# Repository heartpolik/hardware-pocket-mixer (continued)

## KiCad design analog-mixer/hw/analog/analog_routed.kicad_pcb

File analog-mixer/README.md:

# analog-mixer — Rev A

Портативний аналоговий стереомікшер Rev A: 4 стереоканали з pan і FX-петлею
(send/return), Master L/R, вихід на навушники, OLED-метри та Mute/Solo через ESP32-C3,
живлення від 2S LiPo з USB-C.

> [!WARNING]
> Стан: крок E — схеми (ERC чистий) і обидві плати розведено, DRC без розривів і порушень міді;
> Gerber, свердління й BOM — у `hw/fab/` ([14-kicad.md](docs/14-kicad.md), п. 6). Плати ще не
> замовлені й не перевірені в залізі. Команди з документації запускати з теки `analog-mixer/`.

## Архітектура

```mermaid
flowchart TB
    subgraph DIG["Цифрова плата (верхня, над задніми джеками)"]
        ESP["ESP32-C3 SuperMini<br/>радіо вимкнене"]
        OLED["OLED 128×64<br/>метри, Mute/CLIP Master"]
        ENC["Енкодер"]
        LED["RGB LED ×5"]
        ADC[("АЦП метрів")]
    end
    subgraph ANA["Аналогова плата (нижня)"]
        IN(["IN1–4, RET<br/>задній торець"])
        CTRL["Фейдери ×7, send ×4,<br/>pan ×4, PHONES"]
        AUD["Буфери, суматори,<br/>ключі DG413"]
        MX["Cherry MX ×6<br/>Mute"]
        PWR["2S LiPo → ±12 V, 5 V"]
        OUT(["MAIN, SEND, PHONES"])
    end
    USB(["USB-C<br/>правий торець"]) --> PWR
    USB -.->|"дані: CH340N → UART"| ESP
    IN --> AUD --> OUT
    CTRL --> AUD
    ESP <-->|"I²C-A"| AUD
    MX --> ESP
    AUD -.->|"DC метрів"| ADC --> ESP
    PWR -->|"5 V"| DIG
    ESP --> OLED & LED
    ENC --> ESP
```

## Хід роботи

```mermaid
flowchart LR
    S0["0. Аналоги"]:::done --> SA["A. Фейдери"]:::done --> SB["B. Механіка"]:::done --> SC["C. Схема"]:::done --> SD["D. Pinout між платами"]:::done --> SE["E. KiCad"]:::now
    classDef done fill:#d4edda,stroke:#2a6
    classDef now fill:#ffe9b3,stroke:#b8860b
```

## Документація

| Документ | Зміст |
|---|---|
| [spec-rev-a.md](docs/spec-rev-a.md) | ТЗ |
| [decisions.md](docs/decisions.md) | Журнал рішень D1–D50, має пріоритет над ТЗ |
| [00-prior-art.md](docs/00-prior-art.md) | Аналоги та схожі проєкти |
| [01-faders.md](docs/01-faders.md) | Фейдери Alps RS45 |
| [02-mixerli-analysis.md](docs/02-mixerli-analysis.md) | Розбір mixerli v2.0.1 |
| [03-power-2s.md](docs/03-power-2s.md) | Живлення 2S |
| [04-mixerli-datasheets.md](docs/04-mixerli-datasheets.md) | Висновки з datasheets mixerli |
| [05-mechanics.md](docs/05-mechanics.md) | Механіка, компоновка, висоти |
| [06-signal-flow.md](docs/06-signal-flow.md) | Signal flow, Mute/Solo, метри, керування |
| [07-gain-structure.md](docs/07-gain-structure.md) | Рівні по тракту, запас, шум, вибір op-amp |
| [08-meter-detector.md](docs/08-meter-detector.md) | Детектор метрів і CLIP |
| [09-sourcing.md](docs/09-sourcing.md) | Наявність і ціни ключових компонентів |
| [10-passives.md](docs/10-passives.md) | Пасивні компоненти: правила, перелік, кількості |
| [11-power.md](docs/11-power.md) | Розрахунок живлення ±12 V і 5 V, час роботи |
| [12-parts.md](docs/12-parts.md) | Вибір решти компонентів |
| [13-interboard.md](docs/13-interboard.md) | Крок D: роз'єм і pinout між платами |
| [calc/](docs/calc/), [sim/](docs/sim/) | Скрипти розрахунків (Python) і симуляцій (ngspice) |
| [hw/lib/](hw/lib/README.md) | Бібліотека KiCad: футпринти з креслень |
| [14-kicad.md](docs/14-kicad.md) | Крок E: як згенеровано схеми й плати, стан ERC/DRC |
| [15-3d.md](docs/15-3d.md) | 3D-моделі й збірка |
| [datasheets/](docs/datasheets/README.md) | Усі datasheets проєкту |

## Походження та ліцензія

Проєкт є похідним від **mixerli** (Stahl, 2023):
<https://github.com/stahlnow/mixerli> (базова версія — коміт `18a4a8e`).

SPDX-License-Identifier: CERN-OHL-S-2.0+

This source describes Open Hardware and is licensed under the CERN-OHL-S v2
or any later version. You may redistribute and modify this source and make
products using it under the terms of the CERN-OHL-S v2 or any later version
(https://ohwr.org/cern_ohl_s_v2.txt). This source is distributed WITHOUT ANY
EXPRESS OR IMPLIED WARRANTY, INCLUDING OF MERCHANTABILITY, SATISFACTORY QUALITY
AND FITNESS FOR A PARTICULAR PURPOSE. Please see the CERN-OHL-S v2 for applicable
conditions.

Source location (original): https://github.com/stahlnow/mixerli
Source location (this project): https://github.com/heartpolik/hardware-pocket-mixer

Згідно з розд. 4 CERN-OHL-S v2, на PCB має бути видно source location.
Повний текст ліцензії: [LICENSE](../LICENSE).

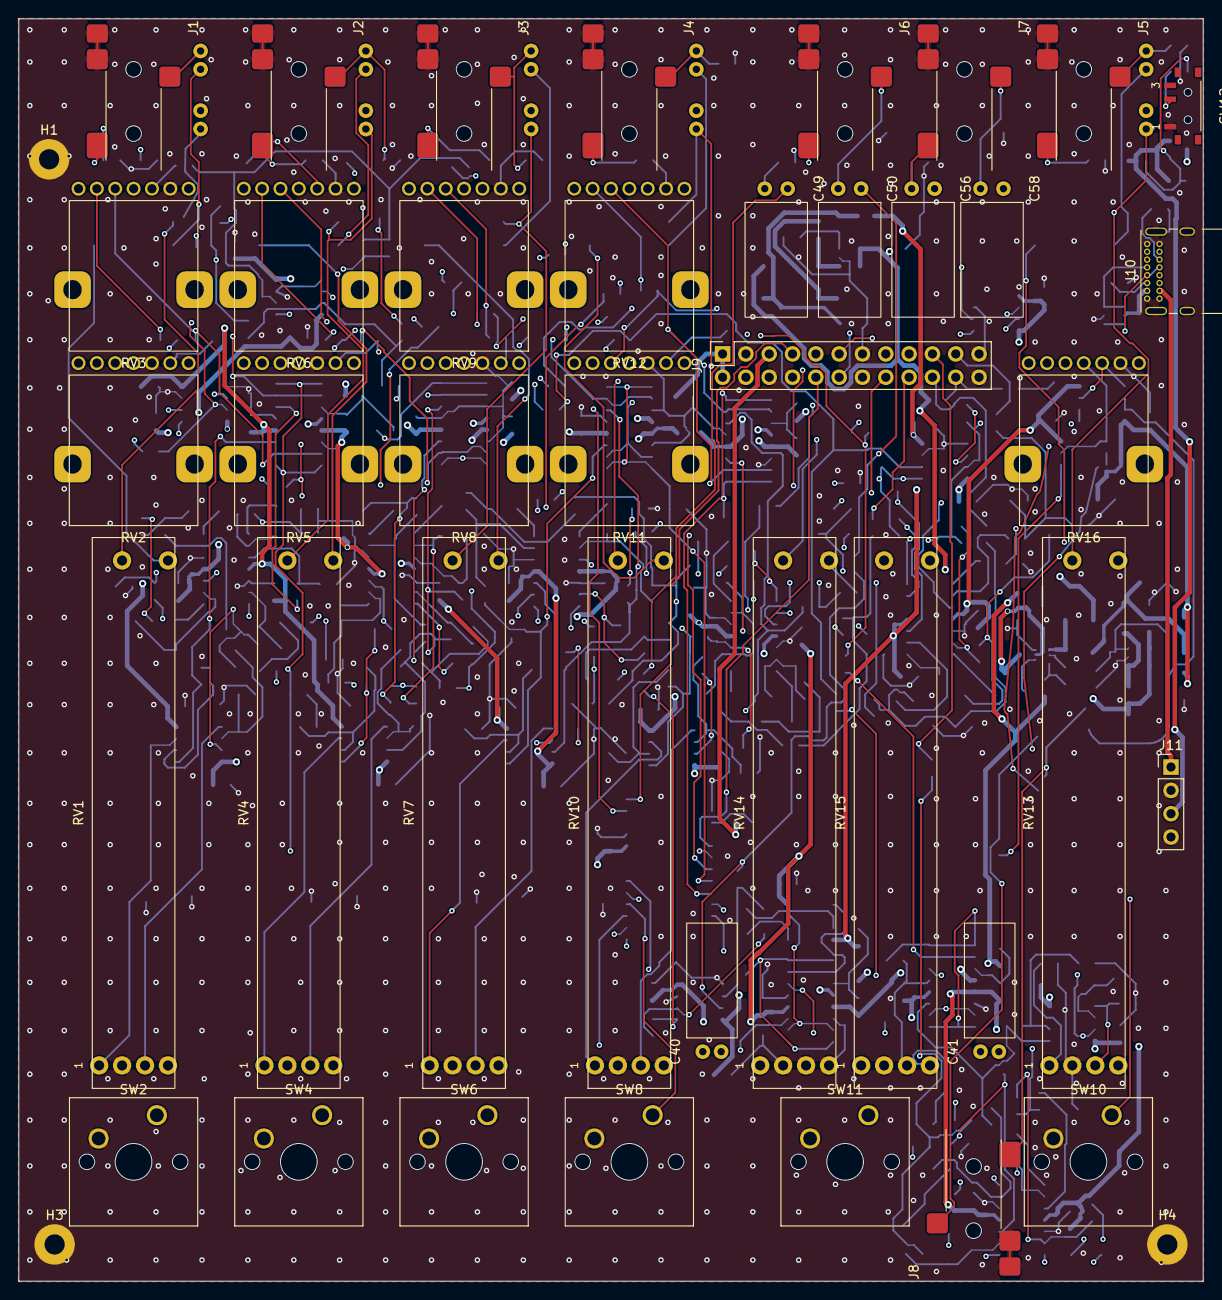
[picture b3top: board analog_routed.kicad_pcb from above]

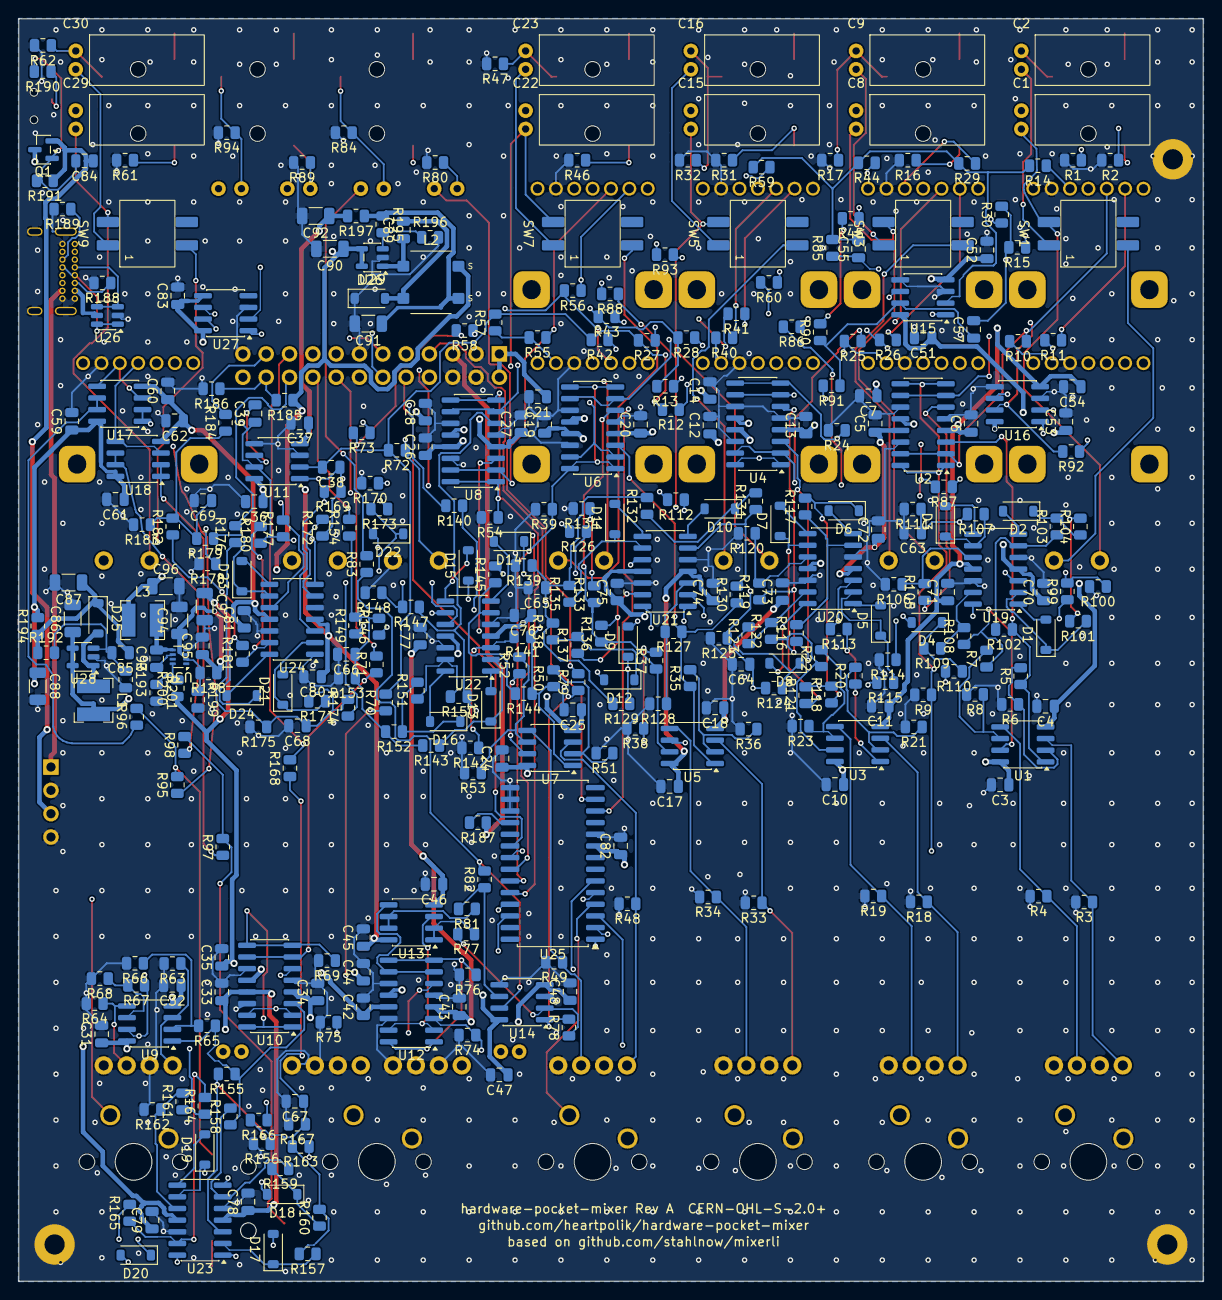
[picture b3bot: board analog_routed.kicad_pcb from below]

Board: 4 copper layers, 129.0 x 137.5 mm, 400 parts (357 on the bottom side), 251 nets.

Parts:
C1, C2, C8, C9, C15, C16, C22, C23, C29, C30, C40, C41: 10u BP; CP_Nichicon_UEP_D5.0_L11.0_P2.00_Horizontal
C3, C4, C5, C6, C7, C10, C11, C12, C13, C14, C17, C18, C19, C20, C21, C24, C25, C26, C27, C28, C31, C32, C33, C34, C35, C36, C37, C42, C43, C44, C45, C46, C47, C48, C51, C52, C53, C54, C59, C60, C61, C62, C70, C71, C72, C73, C74, C75, C76, C77, C78, C79, C80, C81, C82, C83, C84, C93, C95: 100n; C_0805_2012Metric
C38, C39: 39p C0G; C_0805_2012Metric
C49, C50, C56, C58: 47u BP; CP_Nichicon_UEP_D6.3_L11.0_P2.50_Horizontal
C55, C57: 150p C0G; C_0805_2012Metric
C63, C64, C65, C66, C67, C68, C69: 0.33u; C_0805_2012Metric
C85: 10p C0G; C_0805_2012Metric
C86, C90: 4.7u 25V; C_1206_3216Metric
C87, C91, C94: 10u 25V; C_1206_3216Metric
C88, C92: 22u 25V; C_1206_3216Metric
C89: 1u 25V; C_0805_2012Metric
C96, C97: 22u 10V; C_1206_3216Metric
D1, D2, D3, D4, D5, D6, D7, D8, D9, D10, D11, D12, D13, D14, D15, D16, D17, D18, D19, D20, D21, D22, D23, D24: 1N4148W; D_SOD-123
D25, D26: MBR0530; D_SOD-123
H1, H3, H4: M2; MountingHole_2.2mm_M2_Pad_Standoff_2Side
J1, J2, J3, J4, J5: SJ-43514-SMT; CUI_SJ-43514-SMT_TRRS_Horizontal
J6: SJ-43514-SMT MAIN; CUI_SJ-43514-SMT_TRRS_Horizontal
J7: SJ-43514-SMT SEND; CUI_SJ-43514-SMT_TRRS_Horizontal
J8: SJ-43514-SMT PHONES; CUI_SJ-43514-SMT_TRRS_Horizontal
J9: PBS-24 до цифрової плати; PinSocket_2x12_P2.54mm_Vertical
J10: GCT USB4085; USB_C_Receptacle_GCT_USB4085
J11: Модуль IP2326: VBUS, GND, BAT+, GND; PinHeader_1x04_P2.54mm_Vertical
L1: 10u SRN4018-100M; L_Bourns-SRN4018
L2: 2x10u CLS62-100; L_Sumida_CLS62
L3: 4.7u SRN4018-4R7M; L_Bourns-SRN4018
Q1: AO3401A; SOT-23
R1, R2, R3, R4, R16, R17, R18, R19, R31, R32, R33, R34, R46, R47, R48, R49, R61, R62, R63, R64, R74, R75: 1M; R_0805_2012Metric
R5, R6, R7, R8, R10, R11, R20, R21, R22, R23, R25, R26, R35, R36, R37, R38, R40, R41, R50, R51, R52, R53, R55, R56, R65, R66, R67, R68, R77, R78, R81, R82, R85, R86, R87, R90, R91, R92, R112, R126, R140, R154, R168, R176, R184, R187, R190, R196: 10k; R_0805_2012Metric
R9, R24, R39, R54, R69, R76, R80, R84, R89, R94, R100, R106, R114, R120, R128, R134, R142, R148, R156, R162, R170, R178, R186, R191, R198, R199: 100k; R_0805_2012Metric
R12, R13, R27, R28, R42, R43, R57, R58: 22k; R_0805_2012Metric
R14, R15, R29, R30, R44, R45, R59, R60: 20k; R_0805_2012Metric
R70, R71: 76.8k; R_0805_2012Metric
R72, R73: 38.3k; R_0805_2012Metric
R79, R83, R88, R93: 100; R_0805_2012Metric
R95, R96, R97, R98: 10; R_0805_2012Metric
R99, R105, R113, R119, R127, R133, R141, R147, R155, R161, R169, R177: 374k; R_0805_2012Metric
R101, R104, R107, R110, R115, R118, R121, R124, R129, R132, R135, R138, R143, R146, R149, R152, R157, R160, R163, R166, R171, R174, R179, R182: 330; R_0805_2012Metric
R102, R108, R116, R122, R130, R136, R144, R150, R158, R164, R172, R180: 953k; R_0805_2012Metric
R103, R109, R117, R123, R131, R137, R145, R151, R159, R165, R173, R181: 200k; R_0805_2012Metric
R111, R125, R139, R153, R167: 634k; R_0805_2012Metric
R175, R183: 412k; R_0805_2012Metric
R185: 249k; R_0805_2012Metric
R188, R189: 5.1k; R_0805_2012Metric
R192: 113k; R_0805_2012Metric
R193: 13.3k; R_0805_2012Metric
R194, R197: 2.2; R_0805_2012Metric
R195: 84.5k; R_0805_2012Metric
R200: 53.6k; R_0805_2012Metric
R201: 10.2k; R_0805_2012Metric
RV1, RV4, RV7, RV10, RV13, RV14, RV15: RS451121400A 10k B; Alps_RS451121400A_Fader_Dual_45mm
RV2, RV5, RV8, RV11: RK14K124003H 10k B detent; Alps_RK14K124_Vertical_Tone
RV3, RV6, RV9, RV12: RK14K12D 50k A; Alps_RK14K12D_Vertical_Volume
RV16: RK14K12D 50k A PHONES; Alps_RK14K12D_Vertical_Volume
SW1, SW3, SW5, SW7, SW9: CTS 204-121ST; CTS_204-121ST_DIP_SPDT_1pos_SMD
SW2, SW4, SW6, SW8, SW10, SW11: Cherry MX; SW_Cherry_MX_1.00u_PCB
SW12: MSK12C02 вимикач живлення; SW_Slide_SPDT_SHOUHAN_MSK12C02_RightAngle
U1, U3, U5, U7, U9, U11, U13, U14, U15, U16, U17, U18: OPA1678; SOIC-8_3.9x4.9mm_P1.27mm
U2, U4, U6, U8, U10, U12: DG413; SOIC-16_3.9x9.9mm_P1.27mm
U19, U20, U21, U22, U23, U24: TL064AC; SOIC-14_3.9x8.7mm_P1.27mm
U25: MCP23017-E/SO; SOIC-28W_7.5x17.9mm_P1.27mm
U26: USBLC6-2SC6; SOT-23-6
U27: CH340N; SOIC-8_3.9x4.9mm_P1.27mm
U28: LT1930ES5; SOT-23-5
U29: LT1931ES5; SOT-23-5
U30: TPS62933O; SOT-583-8

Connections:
/+3V3: C82.1, C83.1, J9.5, R187.1, U25.9, U27.5, U27.8
/+5V: C7.1, C14.1, C21.1, C28.1, C35.1, C44.1, C96.1, C97.1, J9.1, J9.2, L3.2, R200.1, U2.12, U4.12, U6.12, U8.12, U10.12, U12.12
/+12VA: C3.1, C5.1, C10.1, C12.1, C17.1, C19.1, C24.1, C26.1, C31.1, C33.1, C36.1, C42.1, C45.1, C47.1, C51.1, C53.1, C59.1, C61.1, C70.1, C72.1, C74.1, C76.1, C78.1, C80.1, C88.1, R194.2, U1.8, U2.13, U3.8, U4.13, U5.8, U6.13, U7.8, U8.13, U9.8, U10.13, U11.8, U12.13, U13.8, U14.8, U15.8, U16.8, U17.8, U18.8, U19.4, U20.4, U21.4, U22.4, U23.4, U24.4
/+12V_P: C85.1, C87.1, D25.1, R192.1, R194.1
/-12VA: C4.1, C6.1, C11.1, C13.1, C18.1, C20.1, C25.1, C27.1, C32.1, C34.1, C37.1, C43.1, C46.1, C48.1, C52.1, C54.1, C60.1, C62.1, C71.1, C73.1, C75.1, C77.1, C79.1, C81.1, C92.1, R197.2, U1.4, U2.4, U3.4, U4.4, U5.4, U6.4, U7.4, U8.4, U9.4, U10.4, U11.4, U12.4, U13.4, U14.4, U15.4, U16.4, U17.4, U18.4, U19.11, U20.11, U21.11, U22.11, U23.11, U24.11
/-12V_P: C91.1, L2.3, R195.1, R197.1
/BAT+: C84.1, J11.3, Q1.2, R191.1
/BST_5: C93.1, U30.6
/BTN_IN1: SW2.1, U25.1
/BTN_IN2: SW4.1, U25.2
/BTN_IN3: SW6.1, U25.3
/BTN_IN4: SW8.1, U25.4
/BTN_M: SW11.1, U25.6
/BTN_RET: SW10.1, U25.5
/CC1: J10.A5, R188.1
/CC2: J10.B5, R189.1
/D_IN1_LN_K: D2.1, R103.2, R104.1
/D_IN1_LN_M: R102.2, R103.1, U19.6
/D_IN1_LN_O: D2.2, U19.7
/D_IN1_LP_IN: R99.2, R100.1, U19.3
/D_IN1_LP_K: D1.1, R101.1, U19.2
/D_IN1_LP_O: D1.2, U19.1
/D_IN1_RN_K: D4.1, R109.2, R110.1
/D_IN1_RN_M: R108.2, R109.1, U19.13
/D_IN1_RN_O: D4.2, U19.14
/D_IN1_RP_IN: R105.2, R106.1, U19.10
/D_IN1_RP_K: D3.1, R107.1, U19.9
/D_IN1_RP_O: D3.2, U19.8
/D_IN2_LN_K: D6.1, R117.2, R118.1
/D_IN2_LN_M: R116.2, R117.1, U20.6
/D_IN2_LN_O: D6.2, U20.7
/D_IN2_LP_IN: R113.2, R114.1, U20.3
/D_IN2_LP_K: D5.1, R115.1, U20.2
/D_IN2_LP_O: D5.2, U20.1
/D_IN2_RN_K: D8.1, R123.2, R124.1
/D_IN2_RN_M: R122.2, R123.1, U20.13
/D_IN2_RN_O: D8.2, U20.14
/D_IN2_RP_IN: R119.2, R120.1, U20.10
/D_IN2_RP_K: D7.1, R121.1, U20.9
/D_IN2_RP_O: D7.2, U20.8
/D_IN3_LN_K: D10.1, R131.2, R132.1
/D_IN3_LN_M: R130.2, R131.1, U21.6
/D_IN3_LN_O: D10.2, U21.7
/D_IN3_LP_IN: R127.2, R128.1, U21.3
/D_IN3_LP_K: D9.1, R129.1, U21.2
/D_IN3_LP_O: D9.2, U21.1
/D_IN3_RN_K: D12.1, R137.2, R138.1
/D_IN3_RN_M: R136.2, R137.1, U21.13
/D_IN3_RN_O: D12.2, U21.14
/D_IN3_RP_IN: R133.2, R134.1, U21.10
/D_IN3_RP_K: D11.1, R135.1, U21.9
/D_IN3_RP_O: D11.2, U21.8
/D_IN4_LN_K: D14.1, R145.2, R146.1
/D_IN4_LN_M: R144.2, R145.1, U22.6
/D_IN4_LN_O: D14.2, U22.7
/D_IN4_LP_IN: R141.2, R142.1, U22.3
/D_IN4_LP_K: D13.1, R143.1, U22.2
/D_IN4_LP_O: D13.2, U22.1
/D_IN4_RN_K: D16.1, R151.2, R152.1
/D_IN4_RN_M: R150.2, R151.1, U22.13
/D_IN4_RN_O: D16.2, U22.14
/D_IN4_RP_IN: R147.2, R148.1, U22.10
/D_IN4_RP_K: D15.1, R149.1, U22.9
/D_IN4_RP_O: D15.2, U22.8
/D_MLN_K: D22.1, R173.2, R174.1
/D_MLN_M: R172.2, R173.1, U24.6
/D_MLN_O: D22.2, U24.7
/D_MLP_IN: R169.2, R170.1, U24.3
/D_MLP_K: D21.1, R171.1, U24.2
/D_MLP_O: D21.2, U24.1
/D_MRN_K: D24.1, R181.2, R182.1
/D_MRN_M: R180.2, R181.1, U24.13
/D_MRN_O: D24.2, U24.14
/D_MRP_IN: R177.2, R178.1, U24.10
/D_MRP_K: D23.1, R179.1, U24.9
/D_MRP_O: D23.2, U24.8
/D_RET_LN_K: D18.1, R159.2, R160.1
/D_RET_LN_M: R158.2, R159.1, U23.6
/D_RET_LN_O: D18.2, U23.7
/D_RET_LP_IN: R155.2, R156.1, U23.3
/D_RET_LP_K: D17.1, R157.1, U23.2
/D_RET_LP_O: D17.2, U23.1
/D_RET_RN_K: D20.1, R165.2, R166.1
/D_RET_RN_M: R164.2, R165.1, U23.13
/D_RET_RN_O: D20.2, U23.14
/D_RET_RP_IN: R161.2, R162.1, U23.10
/D_RET_RP_K: D19.1, R163.1, U23.9
/D_RET_RP_O: D19.2, U23.8
/EN_5: R198.2, R199.1, U30.2
/FB_5: R200.2, R201.1, U30.8
/FB_N: R195.2, R196.1, U29.3
/FB_P: C85.2, R192.2, R193.1, U28.3
/GND: C3.2, C4.2, C5.2, C6.2, C7.2, C10.2, C11.2, C12.2, C13.2, C14.2, C17.2, C18.2, C19.2, C20.2, C21.2, C24.2, C25.2, C26.2, C27.2, C28.2, C31.2, C32.2, C33.2, C34.2, C35.2, C36.2, C37.2, C42.2, C43.2, C44.2, C45.2, C46.2, C47.2, C48.2, C51.2, C52.2, C53.2, C54.2, C59.2, C60.2, C61.2, C62.2, C63.2, C64.2, C65.2, C66.2, C67.2, C68.2, C69.2, C70.2, C71.2, C72.2, C73.2, C74.2, C75.2, C76.2, C77.2, C78.2, C79.2, C80.2, C81.2, C82.2, C83.2, C86.2, C87.2, C88.2, C90.2, C91.2, C92.2, C94.2, C95.2, C96.2, C97.2, D26.1, H1.1, H3.1, H4.1, J1.1, J1.4, J2.1, J2.4, J3.1, J3.4, J4.1, J4.4, J5.1, J5.4, J6.1, J6.4, J7.1, J7.4, J8.1, J8.4, J9.3, J9.4, J9.6, J9.8, J9.13, J9.14, J9.23, J9.24, J10.A1, J10.A12, J10.B1, J10.B12, J10.SH, J11.2, J11.4, R1.2, R2.2, R3.2, R4.2, R6.2, R8.2, R9.2, R16.2, R17.2, R18.2, R19.2, R21.2, R23.2, R24.2, R31.2, R32.2, R33.2, R34.2, R36.2, R38.2, R39.2, R46.2, R47.2, R48.2, R49.2, R51.2, R53.2, R54.2, R61.2, R62.2, R63.2, R64.2, R66.2, R68.2, R69.2, R74.2, R75.2, R76.2, R80.2, R84.2, R89.2, R94.2, R100.2, R106.2, R111.2, R114.2, R120.2, R125.2, R128.2, R134.2, R139.2, R142.2, R148.2, R153.2, R156.2, R162.2, R167.2, R170.2, R175.2, R178.2, R183.2, R186.2, R188.2, R189.2, R193.2, R196.2, R199.2, R201.2, RV1.1, RV1.4, RV2.2, RV3.1, RV4.1, RV4.4, RV5.2, RV6.1, RV7.1, RV7.4, RV8.2, RV9.1, RV10.1, RV10.4, RV11.2, RV12.1, RV13.1, RV13.4, RV14.1, RV14.4, RV14.5, RV14.6, RV15.1, RV15.4, RV15.5, RV15.6, RV16.1, SW2.2, SW4.2, SW6.2, SW8.2, SW10.2, SW11.2, SW12.1, U2.5, U2.11, U2.14, U4.5, U4.11, U4.14, U6.5, U6.11, U6.14, U8.5, U8.11, U8.14, U10.5, U10.11, U10.14, U11.3, U11.5, U12.5, U12.11, U12.14, U14.3, U14.5, U15.3, U15.5, U16.3, U16.5, U19.5, U19.12, U20.5, U20.12, U21.5, U21.12, U22.5, U22.12, U23.5, U23.12, U24.5, U24.12, U25.10, U25.15, U25.16, U25.17, U26.2, U27.3, U28.2, U29.2, U30.4
/I2C_A_SCL: J9.9, U25.12
/I2C_A_SDA: J9.7, U25.13
/IN1_LB: R5.1, R99.1, R102.1, U1.1, U2.3
/IN1_LFB: R5.2, R6.1, U1.2
/IN1_LM: R10.1, RV3.3, U2.2, U2.15
/IN1_LP: R10.2, R12.1, RV2.1
/IN1_LS: R14.1, RV3.2
/IN1_LW: R3.1, RV1.2, U1.3
/IN1_R: C2.1, J1.3, R2.1
/IN1_RB: R7.1, R105.1, R108.1, U1.7, U2.6
/IN1_RC: C2.2, SW1.4
/IN1_RFB: R7.2, R8.1, U1.6
/IN1_RM: R11.1, RV3.6, U2.7, U2.10
/IN1_RP: R11.2, R13.1, RV2.3
/IN1_RS: R15.1, RV3.5
/IN1_RTOP: RV1.6, SW1.1
/IN1_RW: R4.1, RV1.5, U1.5
/IN1_T: C1.1, J1.2, R1.1
/IN1_TC: C1.2, RV1.3, SW1.3
/IN2_LB: R20.1, R113.1, R116.1, U3.1, U4.3
/IN2_LFB: R20.2, R21.1, U3.2
/IN2_LM: R25.1, RV6.3, U4.2, U4.15
/IN2_LP: R25.2, R27.1, RV5.1
/IN2_LS: R29.1, RV6.2
/IN2_LW: R18.1, RV4.2, U3.3
/IN2_R: C9.1, J2.3, R17.1
/IN2_RB: R22.1, R119.1, R122.1, U3.7, U4.6
/IN2_RC: C9.2, SW3.4
/IN2_RFB: R22.2, R23.1, U3.6
/IN2_RM: R26.1, RV6.6, U4.7, U4.10
/IN2_RP: R26.2, R28.1, RV5.3
/IN2_RS: R30.1, RV6.5
/IN2_RTOP: RV4.6, SW3.1
/IN2_RW: R19.1, RV4.5, U3.5
/IN2_T: C8.1, J2.2, R16.1
/IN2_TC: C8.2, RV4.3, SW3.3
/IN3_LB: R35.1, R127.1, R130.1, U5.1, U6.3
/IN3_LFB: R35.2, R36.1, U5.2
/IN3_LM: R40.1, RV9.3, U6.2, U6.15
/IN3_LP: R40.2, R42.1, RV8.1
/IN3_LS: R44.1, RV9.2
/IN3_LW: R33.1, RV7.2, U5.3
/IN3_R: C16.1, J3.3, R32.1
/IN3_RB: R37.1, R133.1, R136.1, U5.7, U6.6
/IN3_RC: C16.2, SW5.4
/IN3_RFB: R37.2, R38.1, U5.6
/IN3_RM: R41.1, RV9.6, U6.7, U6.10
/IN3_RP: R41.2, R43.1, RV8.3
/IN3_RS: R45.1, RV9.5
/IN3_RTOP: RV7.6, SW5.1
/IN3_RW: R34.1, RV7.5, U5.5
/IN3_T: C15.1, J3.2, R31.1
/IN3_TC: C15.2, RV7.3, SW5.3
/IN4_LB: R50.1, R141.1, R144.1, U7.1, U8.3
/IN4_LFB: R50.2, R51.1, U7.2
/IN4_LM: R55.1, RV12.3, U8.2, U8.15
/IN4_LP: R55.2, R57.1, RV11.1
/IN4_LS: R59.1, RV12.2
/IN4_LW: R48.1, RV10.2, U7.3
/IN4_R: C23.1, J4.3, R47.1
/IN4_RB: R52.1, R147.1, R150.1, U7.7, U8.6
/IN4_RC: C23.2, SW7.4
/IN4_RFB: R52.2, R53.1, U7.6
/IN4_RM: R56.1, RV12.6, U8.7, U8.10
/IN4_RP: R56.2, R58.1, RV11.3
/IN4_RS: R60.1, RV12.5
/IN4_RTOP: RV10.6, SW7.1
/IN4_RW: R49.1, RV10.5, U7.5
/IN4_T: C22.1, J4.2, R46.1
/IN4_TC: C22.2, RV10.3, SW7.3
/INT_N: J9.10, U25.20
/MAIN_L: C49.2, J6.2, R80.1
/MAIN_R: C50.2, J6.3, R84.1
/MCP_RST: R187.2, U25.18
/ML_B: R77.1, U13.1, U13.2
/ML_C: C40.2, R74.1, U12.3
/ML_INV: R77.2, R78.1, U14.2
/ML_M: U12.2, U12.15, U13.3
/ML_O: C49.1, R79.2
/ML_OUT: R78.2, R79.1, U14.1
/ML_W: C40.1, RV14.2
/MR_B: R81.1, U13.6, U13.7
/MR_C: C41.2, R75.1, U12.6
/MR_INV: R81.2, R82.1, U14.6
/MR_M: U12.7, U12.10, U13.5
/MR_O: C50.1, R83.2
/MR_OUT: R82.2, R83.1, U14.7
/MR_W: C41.1, RV15.2
/MTR_CH1: J9.15, R112.2
/MTR_CH1_H: C63.1, R101.2, R104.2, R107.2, R110.2, R111.1, R112.1
/MTR_CH2: J9.16, R126.2
/MTR_CH2_H: C64.1, R115.2, R118.2, R121.2, R124.2, R125.1, R126.1
/MTR_CH3: J9.17, R140.2
/MTR_CH3_H: C65.1, R129.2, R132.2, R135.2, R138.2, R139.1, R140.1
/MTR_CH4: J9.18, R154.2
/MTR_CH4_H: C66.1, R143.2, R146.2, R149.2, R152.2, R153.1, R154.1
/MTR_ML: J9.20, R176.2
/MTR_ML_H: C68.1, R171.2, R174.2, R175.1, R176.1
/MTR_MR: J9.21, R184.2
/MTR_MR_H: C69.1, R179.2, R182.2, R183.1, R184.1
/MTR_RET: J9.19, R168.2
/MTR_RET_H: C67.1, R157.2, R160.2, R163.2, R166.2, R167.1, R168.1
/MUTE_IN1: R9.1, U2.1, U2.8, U2.9, U2.16, U25.21
/MUTE_IN2: R24.1, U4.1, U4.8, U4.9, U4.16, U25.22
/MUTE_IN3: R39.1, U6.1, U6.8, U6.9, U6.16, U25.23
/MUTE_IN4: R54.1, U8.1, U8.8, U8.9, U8.16, U25.24
/MUTE_M: R76.1, U12.1, U12.8, U12.9, U12.16, U25.26
/MUTE_RET: R69.1, U10.1, U10.8, U10.9, U10.16, U25.25
/N_N: C89.2, D26.2, L2.4
/PH_L: J8.2, R95.2, R96.2
/PH_LA: R95.1, U17.1, U17.2
/PH_LB: R96.1, U17.6, U17.7
/PH_LW: RV16.2, U17.3, U17.5
/PH_R: J8.3, R97.2, R98.2
/PH_RA: R97.1, U18.1, U18.2
/PH_RB: R98.1, U18.6, U18.7
/PH_RW: RV16.5, U18.3, U18.5
/PWR_G: C84.2, Q1.1, R190.2, R191.2
/PWR_G_SW: R190.1, SW12.2
/RET_LB: R65.1, R155.1, R158.1, U9.1, U10.3
/RET_LFB: R65.2, R66.1, U9.2
/RET_LM: R70.1, U10.2, U10.15
/RET_LW: R63.1, RV13.2, U9.3
/RET_R: C30.1, J5.3, R62.1
/RET_RB: R67.1, R161.1, R164.1, U9.7, U10.6
/RET_RC: C30.2, SW9.4
/RET_RFB: R67.2, R68.1, U9.6
/RET_RM: R71.1, U10.7, U10.10
/RET_RTOP: RV13.6, SW9.1
/RET_RW: R64.1, RV13.5, U9.5
/RET_T: C29.1, J5.2, R61.1
/RET_TC: C29.2, RV13.3, SW9.3
/SEND_L: C56.2, J7.2, R89.1
/SEND_L_IN: C55.2, R14.2, R29.2, R44.2, R59.2, R85.2, U15.2
/SEND_L_INV: R86.2, R87.1, U16.2
/SEND_L_O: C56.1, R88.2
/SEND_L_OUT: R87.2, R88.1, U16.1
/SEND_L_S: C55.1, R85.1, R86.1, U15.1
/SEND_R: C58.2, J7.3, R94.1
/SEND_R_IN: C57.2, R15.2, R30.2, R45.2, R60.2, R90.2, U15.6
/SEND_R_INV: R91.2, R92.1, U16.6
/SEND_R_O: C58.1, R93.2
/SEND_R_OUT: R92.2, R93.1, U16.7
/SEND_R_S: C57.1, R90.1, R91.1, U15.7
/SUM_L: C38.1, R72.1, R169.1, R172.1, RV14.3, RV16.3, U11.1
/SUM_L_IN: C38.2, R12.2, R27.2, R42.2, R57.2, R70.2, R72.2, U11.2
/SUM_R: C39.1, R73.1, R177.1, R180.1, RV15.3, RV16.6, U11.7
/SUM_R_IN: C39.2, R13.2, R28.2, R43.2, R58.2, R71.2, R73.2, U11.6
/SW_5: C93.2, L3.1, U30.5
/SW_N: C89.1, L2.2, U29.1
/SW_P: D25.2, L1.2, U28.1
/UART_RX: J9.12, U27.6
/UART_TX: J9.11, U27.7
/USB_DN: J10.A7, J10.B7, U26.3, U26.4, U27.2
/USB_DP: J10.A6, J10.B6, U26.1, U26.6, U27.1
/VBAT_SENSE: J9.22, R185.2, R186.1
/VBUS: J10.A4, J10.A9, J10.B4, J10.B9, J11.1, U26.5
/VSW: C86.1, C90.1, C94.1, C95.1, L1.1, L2.1, Q1.3, R185.1, R198.1, U28.4, U28.5, U29.4, U29.5, U30.3

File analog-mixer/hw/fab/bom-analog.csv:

Плата,К-сть,Номінал,Footprint,Тип,Позначення
analog,12,10u BP,diy-mixer:CP_Nichicon_UEP_D5.0_L11.0_P2.00_Horizontal,"Nichicon UEP1E100MDD, 25 V (D44)","C1,C2,C8,C9,C15,C16,C22,C23,C29,C30,C40,C41"
analog,59,100n,Capacitor_SMD:C_0805_2012Metric,"X7R, ≥ 25 V (шини ±12 V)","C3,C4,C5,C6,C7,C10,C11,C12,C13,C14,C17,C18,C19,C20,C21,C24,C25,C26,C27,C28,C31,C32,C33,C34,C35,C36,C37,C42,C43,C44,C45,C46,C47,C48,C51,C52,C53,C54,C59,C60,C61,C62,C70,C71,C72,C73,C74,C75,C76,C77,C78,C79,C80,C81,C82,C83,C84,C93,C95"
analog,2,39p C0G,Capacitor_SMD:C_0805_2012Metric,C0G,"C38,C39"
analog,4,47u BP,diy-mixer:CP_Nichicon_UEP_D6.3_L11.0_P2.50_Horizontal,"Nichicon UEP1E470MED, 25 V (10-passives)","C49,C50,C56,C58"
analog,2,150p C0G,Capacitor_SMD:C_0805_2012Metric,C0G,"C55,C57"
analog,7,0.33u,Capacitor_SMD:C_0805_2012Metric,"X7R, ≥ 25 V (шини ±12 V)","C63,C64,C65,C66,C67,C68,C69"
analog,1,10p C0G,Capacitor_SMD:C_0805_2012Metric,C0G,C85
analog,2,4.7u 25V,Capacitor_SMD:C_1206_3216Metric,X7R,"C86,C90"
analog,3,10u 25V,Capacitor_SMD:C_1206_3216Metric,X7R,"C87,C91,C94"
analog,2,22u 25V,Capacitor_SMD:C_1206_3216Metric,X7R,"C88,C92"
analog,1,1u 25V,Capacitor_SMD:C_0805_2012Metric,X7R,C89
analog,2,22u 10V,Capacitor_SMD:C_1206_3216Metric,X7R,"C96,C97"
analog,24,1N4148W,Diode_SMD:D_SOD-123,,"D1,D2,D3,D4,D5,D6,D7,D8,D9,D10,D11,D12,D13,D14,D15,D16,D17,D18,D19,D20,D21,D22,D23,D24"
analog,2,MBR0530,Diode_SMD:D_SOD-123,,"D25,D26"
analog,5,SJ-43514-SMT,diy-mixer:CUI_SJ-43514-SMT_TRRS_Horizontal,,"J1,J2,J3,J4,J5"
analog,1,SJ-43514-SMT MAIN,diy-mixer:CUI_SJ-43514-SMT_TRRS_Horizontal,,J6
analog,1,SJ-43514-SMT SEND,diy-mixer:CUI_SJ-43514-SMT_TRRS_Horizontal,,J7
analog,1,SJ-43514-SMT PHONES,diy-mixer:CUI_SJ-43514-SMT_TRRS_Horizontal,,J8
analog,1,PBS-24 до цифрової плати,Connector_PinSocket_2.54mm:PinSocket_2x12_P2.54mm_Vertical,,J9
analog,1,GCT USB4085,Connector_USB:USB_C_Receptacle_GCT_USB4085,,J10
analog,1,"Модуль IP2326: VBUS, GND, BAT+, GND",Connector_PinHeader_2.54mm:PinHeader_1x04_P2.54mm_Vertical,,J11
analog,1,10u SRN4018-100M,Inductor_SMD:L_Bourns-SRN4018,,L1
analog,1,2x10u CLS62-100,diy-mixer:L_Sumida_CLS62,,L2
analog,1,4.7u SRN4018-4R7M,Inductor_SMD:L_Bourns-SRN4018,,L3
analog,1,AO3401A,Package_TO_SOT_SMD:SOT-23,,Q1
analog,22,1M,Resistor_SMD:R_0805_2012Metric,"товстоплівковий 1 %, E96","R1,R2,R3,R4,R16,R17,R18,R19,R31,R32,R33,R34,R46,R47,R48,R49,R61,R62,R63,R64,R74,R75"
analog,48,10k,Resistor_SMD:R_0805_2012Metric,"товстоплівковий 1 %, E96","R5,R6,R7,R8,R10,R11,R20,R21,R22,R23,R25,R26,R35,R36,R37,R38,R40,R41,R50,R51,R52,R53,R55,R56,R65,R66,R67,R68,R77,R78,R81,R82,R85,R86,R87,R90,R91,R92,R112,R126,R140,R154,R168,R176,R184,R187,R190,R196"
analog,26,100k,Resistor_SMD:R_0805_2012Metric,"товстоплівковий 1 %, E96","R9,R24,R39,R54,R69,R76,R80,R84,R89,R94,R100,R106,R114,R120,R128,R134,R142,R148,R156,R162,R170,R178,R186,R191,R198,R199"
analog,8,22k,Resistor_SMD:R_0805_2012Metric,"товстоплівковий 1 %, E96","R12,R13,R27,R28,R42,R43,R57,R58"
analog,8,20k,Resistor_SMD:R_0805_2012Metric,"товстоплівковий 1 %, E96","R14,R15,R29,R30,R44,R45,R59,R60"
analog,2,76.8k,Resistor_SMD:R_0805_2012Metric,"товстоплівковий 1 %, E96","R70,R71"
analog,2,38.3k,Resistor_SMD:R_0805_2012Metric,"товстоплівковий 1 %, E96","R72,R73"
analog,4,100,Resistor_SMD:R_0805_2012Metric,"товстоплівковий 1 %, E96","R79,R83,R88,R93"
analog,4,10,Resistor_SMD:R_0805_2012Metric,"товстоплівковий 1 %, E96","R95,R96,R97,R98"
analog,12,374k,Resistor_SMD:R_0805_2012Metric,"товстоплівковий 1 %, E96","R99,R105,R113,R119,R127,R133,R141,R147,R155,R161,R169,R177"
analog,24,330,Resistor_SMD:R_0805_2012Metric,"товстоплівковий 1 %, E96","R101,R104,R107,R110,R115,R118,R121,R124,R129,R132,R135,R138,R143,R146,R149,R152,R157,R160,R163,R166,R171,R174,R179,R182"
analog,12,953k,Resistor_SMD:R_0805_2012Metric,"товстоплівковий 1 %, E96","R102,R108,R116,R122,R130,R136,R144,R150,R158,R164,R172,R180"
analog,12,200k,Resistor_SMD:R_0805_2012Metric,"товстоплівковий 1 %, E96","R103,R109,R117,R123,R131,R137,R145,R151,R159,R165,R173,R181"
analog,5,634k,Resistor_SMD:R_0805_2012Metric,"товстоплівковий 1 %, E96","R111,R125,R139,R153,R167"
analog,2,412k,Resistor_SMD:R_0805_2012Metric,"товстоплівковий 1 %, E96","R175,R183"
analog,1,249k,Resistor_SMD:R_0805_2012Metric,"товстоплівковий 1 %, E96",R185
analog,2,5.1k,Resistor_SMD:R_0805_2012Metric,"товстоплівковий 1 %, E96","R188,R189"
analog,1,113k,Resistor_SMD:R_0805_2012Metric,"товстоплівковий 1 %, E96",R192
analog,1,13.3k,Resistor_SMD:R_0805_2012Metric,"товстоплівковий 1 %, E96",R193
analog,2,2.2,Resistor_SMD:R_0805_2012Metric,"товстоплівковий 1 %, E96","R194,R197"
analog,1,84.5k,Resistor_SMD:R_0805_2012Metric,"товстоплівковий 1 %, E96",R195
analog,1,53.6k,Resistor_SMD:R_0805_2012Metric,"товстоплівковий 1 %, E96",R200
analog,1,10.2k,Resistor_SMD:R_0805_2012Metric,"товстоплівковий 1 %, E96",R201
analog,7,RS451121400A 10k B,diy-mixer:Alps_RS451121400A_Fader_Dual_45mm,,"RV1,RV4,RV7,RV10,RV13,RV14,RV15"
analog,4,RK14K124003H 10k B detent,diy-mixer:Alps_RK14K124_Vertical_Tone,,"RV2,RV5,RV8,RV11"
analog,4,RK14K12D 50k A,diy-mixer:Alps_RK14K12D_Vertical_Volume,,"RV3,RV6,RV9,RV12"
analog,1,RK14K12D 50k A PHONES,diy-mixer:Alps_RK14K12D_Vertical_Volume,,RV16
analog,5,CTS 204-121ST,diy-mixer:CTS_204-121ST_DIP_SPDT_1pos_SMD,,"SW1,SW3,SW5,SW7,SW9"
analog,6,Cherry MX,Button_Switch_Keyboard:SW_Cherry_MX_1.00u_PCB,,"SW2,SW4,SW6,SW8,SW10,SW11"
analog,1,MSK12C02 вимикач живлення,diy-mixer:SW_Slide_SPDT_SHOUHAN_MSK12C02_RightAngle,,SW12
analog,12,OPA1678,Package_SO:SOIC-8_3.9x4.9mm_P1.27mm,,"U1,U3,U5,U7,U9,U11,U13,U14,U15,U16,U17,U18"
analog,6,DG413,Package_SO:SOIC-16_3.9x9.9mm_P1.27mm,,"U2,U4,U6,U8,U10,U12"
analog,6,TL064AC,Package_SO:SOIC-14_3.9x8.7mm_P1.27mm,,"U19,U20,U21,U22,U23,U24"
analog,1,MCP23017-E/SO,Package_SO:SOIC-28W_7.5x17.9mm_P1.27mm,,U25
analog,1,USBLC6-2SC6,Package_TO_SOT_SMD:SOT-23-6,,U26
analog,1,CH340N,Package_SO:SOIC-8_3.9x4.9mm_P1.27mm,,U27
analog,1,LT1930ES5,Package_TO_SOT_SMD:SOT-23-5,,U28
analog,1,LT1931ES5,Package_TO_SOT_SMD:SOT-23-5,,U29
analog,1,TPS62933O,Package_TO_SOT_SMD:SOT-583-8,,U30

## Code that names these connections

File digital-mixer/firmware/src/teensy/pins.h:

// SPDX-License-Identifier: GPL-3.0-or-later
// Teensy 4.1 pins as wired in hw/sch/main.py (symbol pins -> Teensy pins: docs/03-schematic.md, p. 2).
#pragma once
#include <stdint.h>

namespace pin {
// SAI1 I2S -> 3 x PCM5102A: BCLK1 21, LRCLK1 20, OUT1A 7 (MAIN), OUT1B 32 (AUX), OUT1C 9 (CUE) - set by AudioOutputI2SHex
// SAI2 TDM <- 2 x PCM1865: BCLK2 4, LRCLK2 3, IN2 5, MCLK2 33 - set by AudioInputTDM2
// I2C (Wire) 18 SDA / 19 SCL: PCM1865 0x4A / 0x4B. I2C2 (Wire2) 25 SDA2 / 24 SCL2: MCP23017 0x20-0x22
constexpr uint8_t MCP_INT[3] = {30, 31, 22};
constexpr uint8_t FADER[4] = {14, 15, 16, 17};          // A0-A3, PTA2043
constexpr uint8_t VBAT = 38;                            // A14 = VSYS / 2
constexpr uint8_t ENC_A = 0, ENC_B = 1, ENC_SW = 2;     // master encoder EC12SY
constexpr uint8_t LCD_SCK = 13, LCD_MOSI = 11, LCD_CS = 10, LCD_DC = 40, LCD_RST = 41, LCD_BLK = 28;
constexpr uint8_t SHIFT = 29;
constexpr uint8_t DAC_XSMT = 36;                        // PCM5102A soft mute, 10k pull-down
constexpr uint8_t HP_EN = 37;                           // TPA6132A2 enable, 10k pull-down
// MIDI OUT: Serial8 TX = 35
}  // namespace pin

// PCM1865 7-bit I2C addresses: MS/AD = GND -> 0x94 (8-bit) = 0x4A, MS/AD = 3V3 -> 0x96 = 0x4B
constexpr uint8_t ADC_ADDR[2] = {0x4A, 0x4B};
constexpr uint8_t MCP_ADDR[3] = {0x20, 0x21, 0x22};

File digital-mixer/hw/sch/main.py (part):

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            "Mic_Bias": None, "VREF": f"ADC{k}_VREF", "AGND": "GND", "AVDD": A3, "XO": None, "XI": "GND",
            "LDO": f"ADC{k}_LDO", "DGND": "GND", "DVDD": D3, "IOVDD": D3, "SCKI": "ADC_MCLK",
            "LRCK": "ADC_LRCK", "BCK": "ADC_BCK", "DOUT": f"ADC{k}_DOUT",
            "GPIO3/INTC": None, "GPIO2/INTB/DMCLK": None, "GPIO1/INTA/DMIN": None, "MISO/GPIO0/DMIN2": None,
            "MOSI/SDA": "I2C_SDA", "MC/SCL": "I2C_SCL", "MS/AD": adr, "MD0": "GND"}, w=50)
        b.c("1u", f"ADC{k}_VREF", "GND")
        b.decouple(A3)
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        b.block(f"MCP23017 #{k} (I²C2, 0x2{k - 1}): енкодери каналів {chs[0]}, {chs[1]} (A/B), Mute; GPx7 вільні; "
                "внутрішні підтяжки 100k, INTA/INTB дзеркальні → один INT", 2)
        spare = {(1, "A"): None, (1, "B"): None, (2, "A"): None, (2, "B"): None}
        pins = {"V_{DD}": D3, "V_{SS}": "GND", "SCK": "I2C2_SCL", "SDA": "I2C2_SDA", "~{RESET}": D3,
                "A0": "GND" if k == 1 else D3, "A1": "GND", "A2": "GND",
                "INTA": f"MCP{k}_INT", "INTB": None, "NC": None}
        for half, ch in zip("AB", chs):
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
    b.block("MCP23017 #3 (I²C2, 0x22): кнопки 12 енкодерів каналів (DM28: натискання — фільтр / компресор, "
            "скидання значення) і кнопки AUX, FX I, FX II (GPA6, GPA7, GPB6) — найближчий до правої колонки; GPB7 вільний", 2)
    pins = {"V_{DD}": D3, "V_{SS}": "GND", "SCK": "I2C2_SCL", "SDA": "I2C2_SDA", "~{RESET}": D3,
            "A0": "GND", "A1": D3, "A2": "GND", "INTA": "MCP3_INT", "INTB": None, "NC": None}
    for half, chs in zip("AB", ((1, 2), (3, 4))):
        for i, (ch, e) in enumerate((c, e) for c in chs for e in range(3)):
            pins[f"GP{half}{i}"] = f"ENC{ch}_{e + 1}_SW"
        pins[f"GP{half}6"] = pins[f"GP{half}7"] = None
    pins.update({"GPA6": "BTN_AUX", "GPA7": "BTN_FX1", "GPB6": "BTN_FX2"})
    b.part("U", "Interface_Expansion:MCP23017x-x-SO", "MCP23017-E/SO", "Package_SO:SOIC-28W_7.5x17.9mm_P1.27mm",
           pins, w=50)
    b.decouple(D3)
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
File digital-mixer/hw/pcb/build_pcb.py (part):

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    u = next(r for r, c in comps.items() if c["value"] == "TPS63802")
    lref = next(r for r, c in comps.items() if c["value"].startswith("0.47u"))
    cin = max((r for r, c in comps.items() if c["value"] == "10u" and
               {n.lstrip("/") for n in c["pins"].values()} == {"VSYS", "GND"}), key=lambda r: int(r[1:]))
    couts = sorted(r for r, c in comps.items() if c["value"] == "22u")
    fp = pcb.fps[u]
    p = {n: pad_xy(fp, n) for n in ("6", "7", "8", "9", "10")}
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        put_pad(pcb, lref, "1", lx, p["9"][1] + 1.2, 270)
    l1, l2 = pad_xy(pcb.fps[lref], "1"), pad_xy(pcb.fps[lref], "2")
    # input cap below the inductor strip, output caps above
    put_pad(pcb, cin, "1" if comps[cin]["pins"]["1"].endswith("VSYS") else "2", xr - 0.2, l1[1] + 2.4, 0)
    cy = l2[1] - 2.4
    for c in couts:
        put_pad(pcb, c, "1" if comps[c]["pins"]["1"].endswith("+4V2") else "2", xr - 0.2, cy, 0)
        cy -= 2.6
    placed |= {lref, cin, *couts}
    vin = pad_xy(pcb.fps[cin], next(n for n, v in comps[cin]["pins"].items() if v.endswith("VSYS")))
    vo = [pad_xy(pcb.fps[c], next(n for n, v in comps[c]["pins"].items() if v.endswith("+4V2"))) for c in couts]
    track(pcb, "/BB_L1", [p["9"], (rx, p["9"][1]), (rx, l1[1]), (l1[0], l1[1])], 0.25)
    track(pcb, "/BB_L2", [p["7"], (rx, p["7"][1]), (rx, l2[1]), (l2[0], l2[1])], 0.25)
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    Returns keep-out boxes of its vias for the bottom-side placement."""
    esd = next(r for r, c in comps.items() if c["value"] == "USBLC6-2SC6")
    teensy = next(r for r, c in comps.items() if "Teensy41" in c["fp"])
    master = next(r for r, c in comps.items() if "EC12SY" in c["fp"] and "/ENC_M_A" in c["pins"].values())
    btn = [r for r, c in comps.items() if "TSF-1266" in c["fp"] and
           any(v.lstrip("/") in ("BTN_AUX", "BTN_FX1", "BTN_FX2") for v in c["pins"].values())]
    dp_pin = pad_xy(pcb.fps[esd], next(n for n, v in comps[esd]["pins"].items() if v.endswith("USB_DP")))
    dn_pin = pad_xy(pcb.fps[esd], next(n for n, v in comps[esd]["pins"].items() if v.endswith("USB_DN")))
    wire_top = min(pcbnew.ToMM(p.GetBoundingBox().GetTop()) - OY for p in pcb.fps[teensy].Pads()
                   if p.GetNumber() in ("66", "67"))
    lug_r = max(pcbnew.ToMM(p.GetBoundingBox().GetRight()) - OX for p in pcb.fps[master].Pads()
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    xc = (lug_r + pad_l) / 2                           # corridor axis
    y_end = wire_top - 2.3                             # stop short of the wire pads
    vx = dp_pin[0] + 1.16                              # vias right of the ESD pins, 0.2 to them and to the USB-C tab
    for net, pin, y_via in (("/USB_DP", dp_pin, dp_pin[1]), ("/USB_DN", dn_pin, dn_pin[1])):
        via(pcb, net, vx, y_via)
        track(pcb, net, [pin, (vx, y_via)], w, pcbnew.B_Cu)
    xs_p, xs_n = xc - h, xc + h
    yfirst = dn_pin[1] + 0.34
    track(pcb, "/USB_DP", [(vx, dp_pin[1]), (xs_p, dp_pin[1]), (xs_p, y_end)], w, pcbnew.F_Cu)
    track(pcb, "/USB_DN", [(vx, dn_pin[1]), (vx + 0.34, yfirst), (xs_n, yfirst), (xs_n, y_end)], w, pcbnew.F_Cu)
    r = 0.3 + 0.4
    return [(vx - r, y - r, vx + r, y + r) for y in (dp_pin[1], dn_pin[1])]

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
